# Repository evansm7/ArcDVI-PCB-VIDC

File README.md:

# ArcDVI VIDC push-on PCB

Kicad 6.0 PCB design for the ArcDVI soldered-VIDC push-on board:

This board carries an upturned PTH PLCC68 which plugs onto a soldered VIDC from above.  This should fit an Acorn A3000, but hasn't been mechanically tested with the other soldered-VIDC machine, A5000.  The board exports the buffered signals over FFC to the ArcDVI main PCB.  Mechanically, the main PCB is designed to bolt on top of this board (with appropriate spacers) and fit underneath the floppy drive.

See <https://stardot.org.uk> for more info.

# License

ArcDVI is copyright 2023 Matt Evans.

This work is licensed under the Creative Commons Attribution-NonCommercial-ShareAlike 3.0 Unported License. To view a copy of this license, visit http://creativecommons.org/licenses/by-nc-sa/3.0/ or send a letter to Creative Commons, PO Box 1866, Mountain View, CA 94042, USA.

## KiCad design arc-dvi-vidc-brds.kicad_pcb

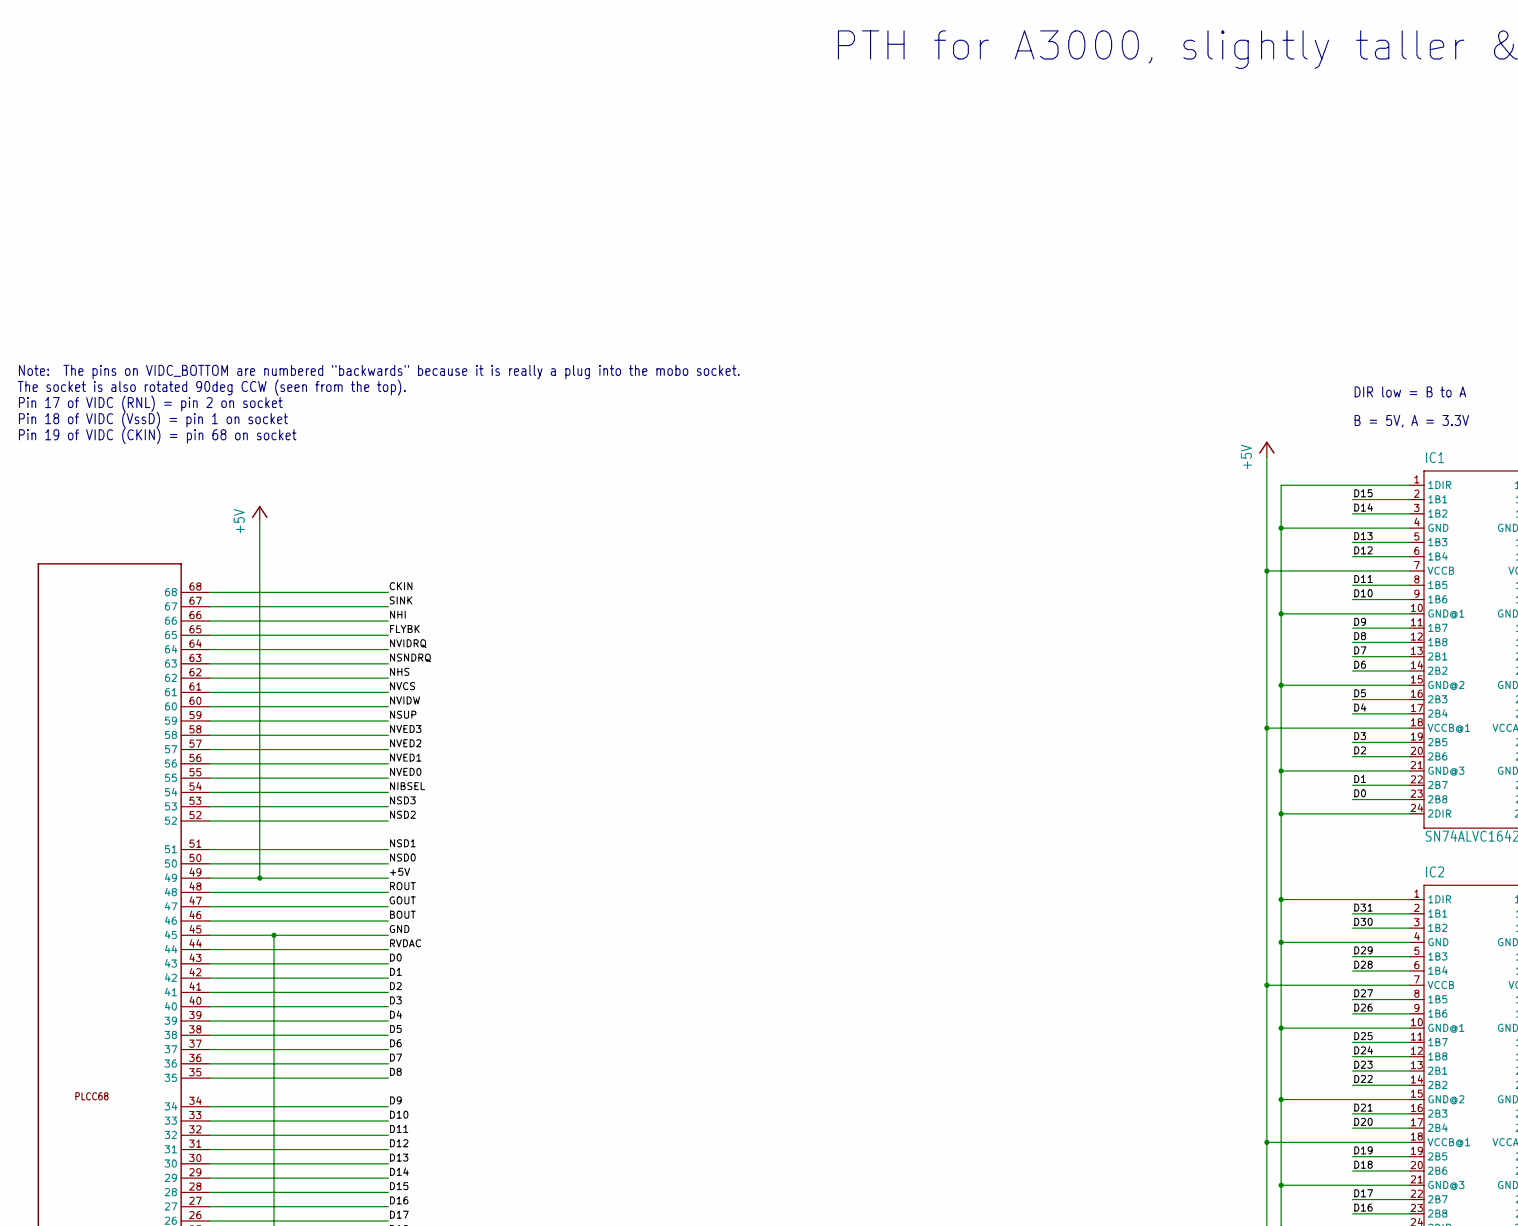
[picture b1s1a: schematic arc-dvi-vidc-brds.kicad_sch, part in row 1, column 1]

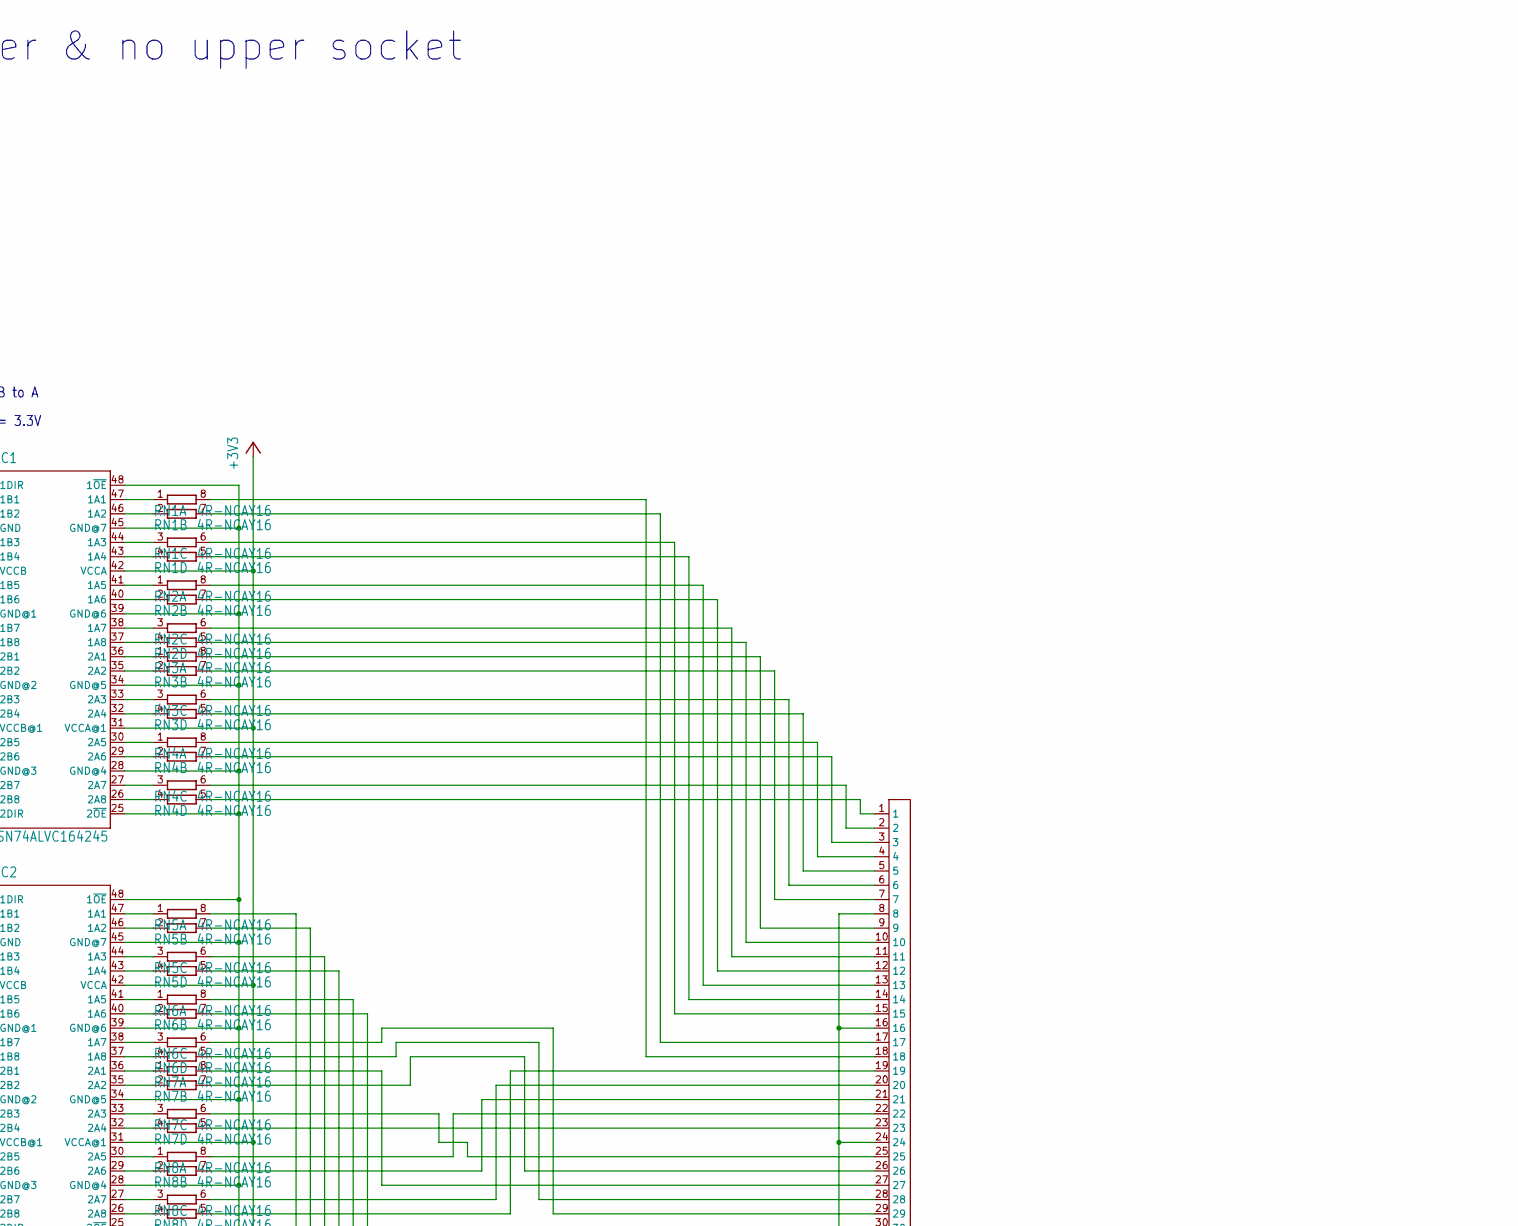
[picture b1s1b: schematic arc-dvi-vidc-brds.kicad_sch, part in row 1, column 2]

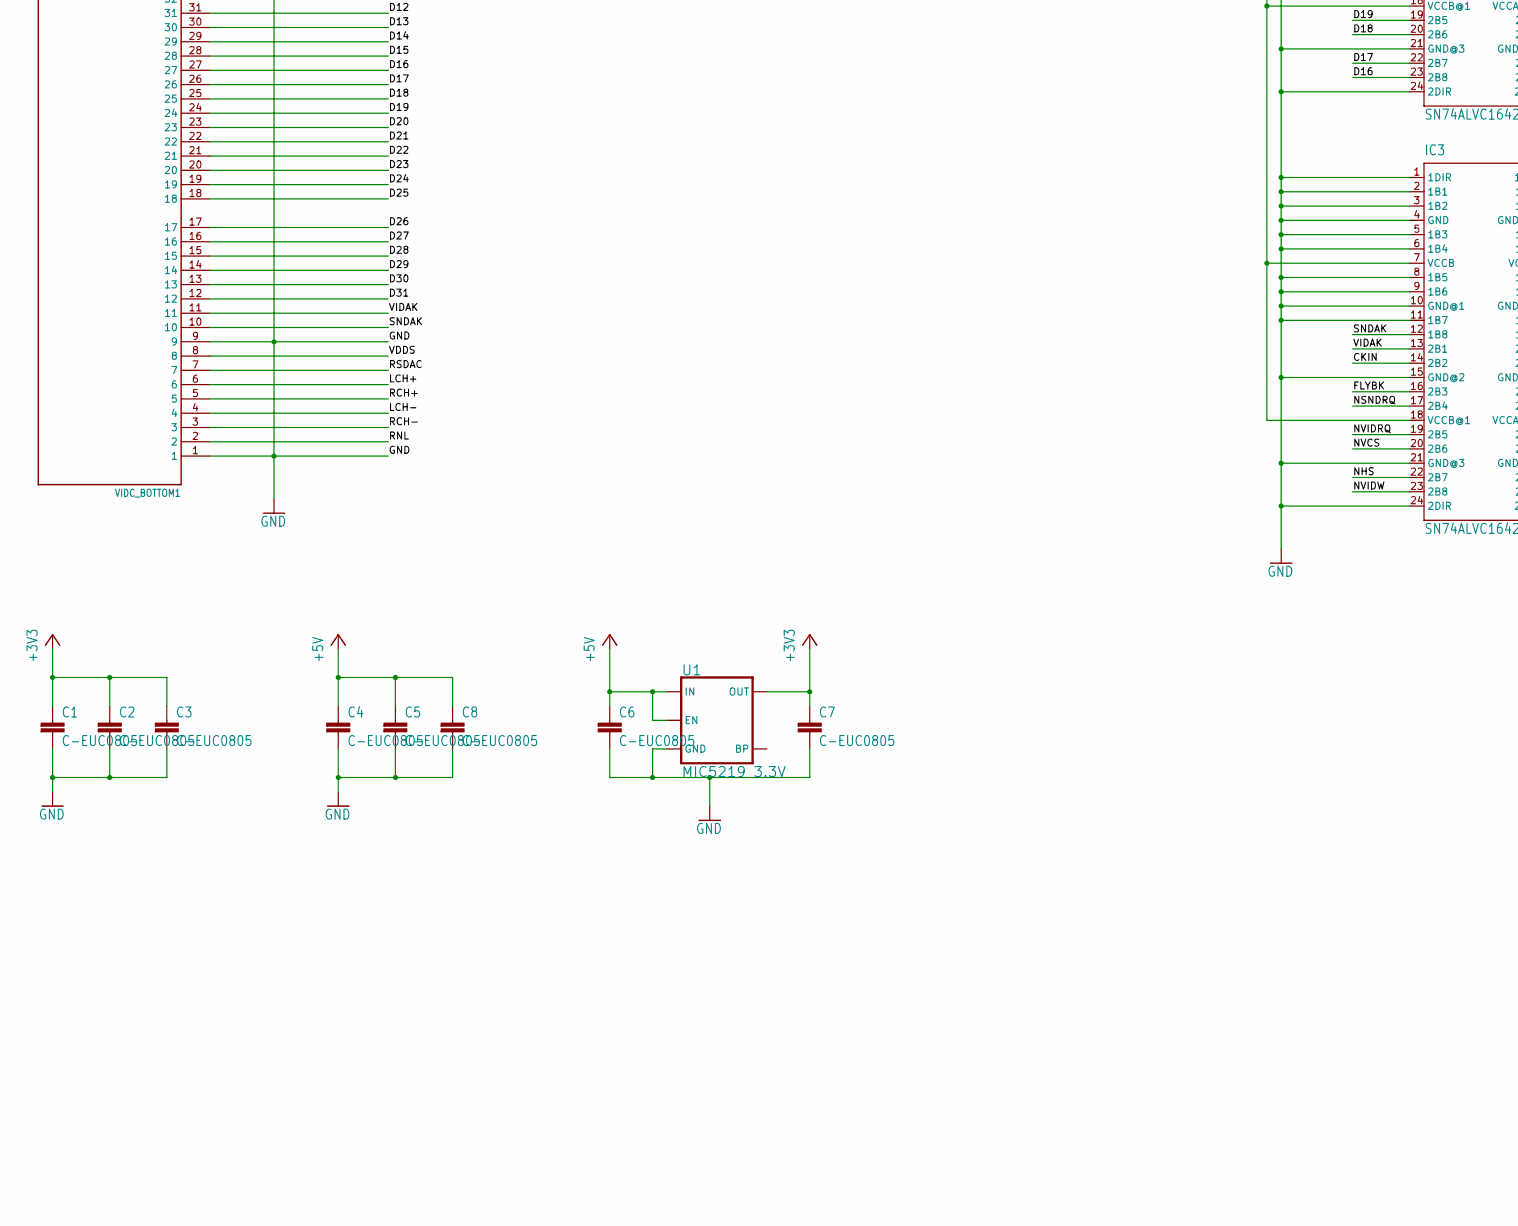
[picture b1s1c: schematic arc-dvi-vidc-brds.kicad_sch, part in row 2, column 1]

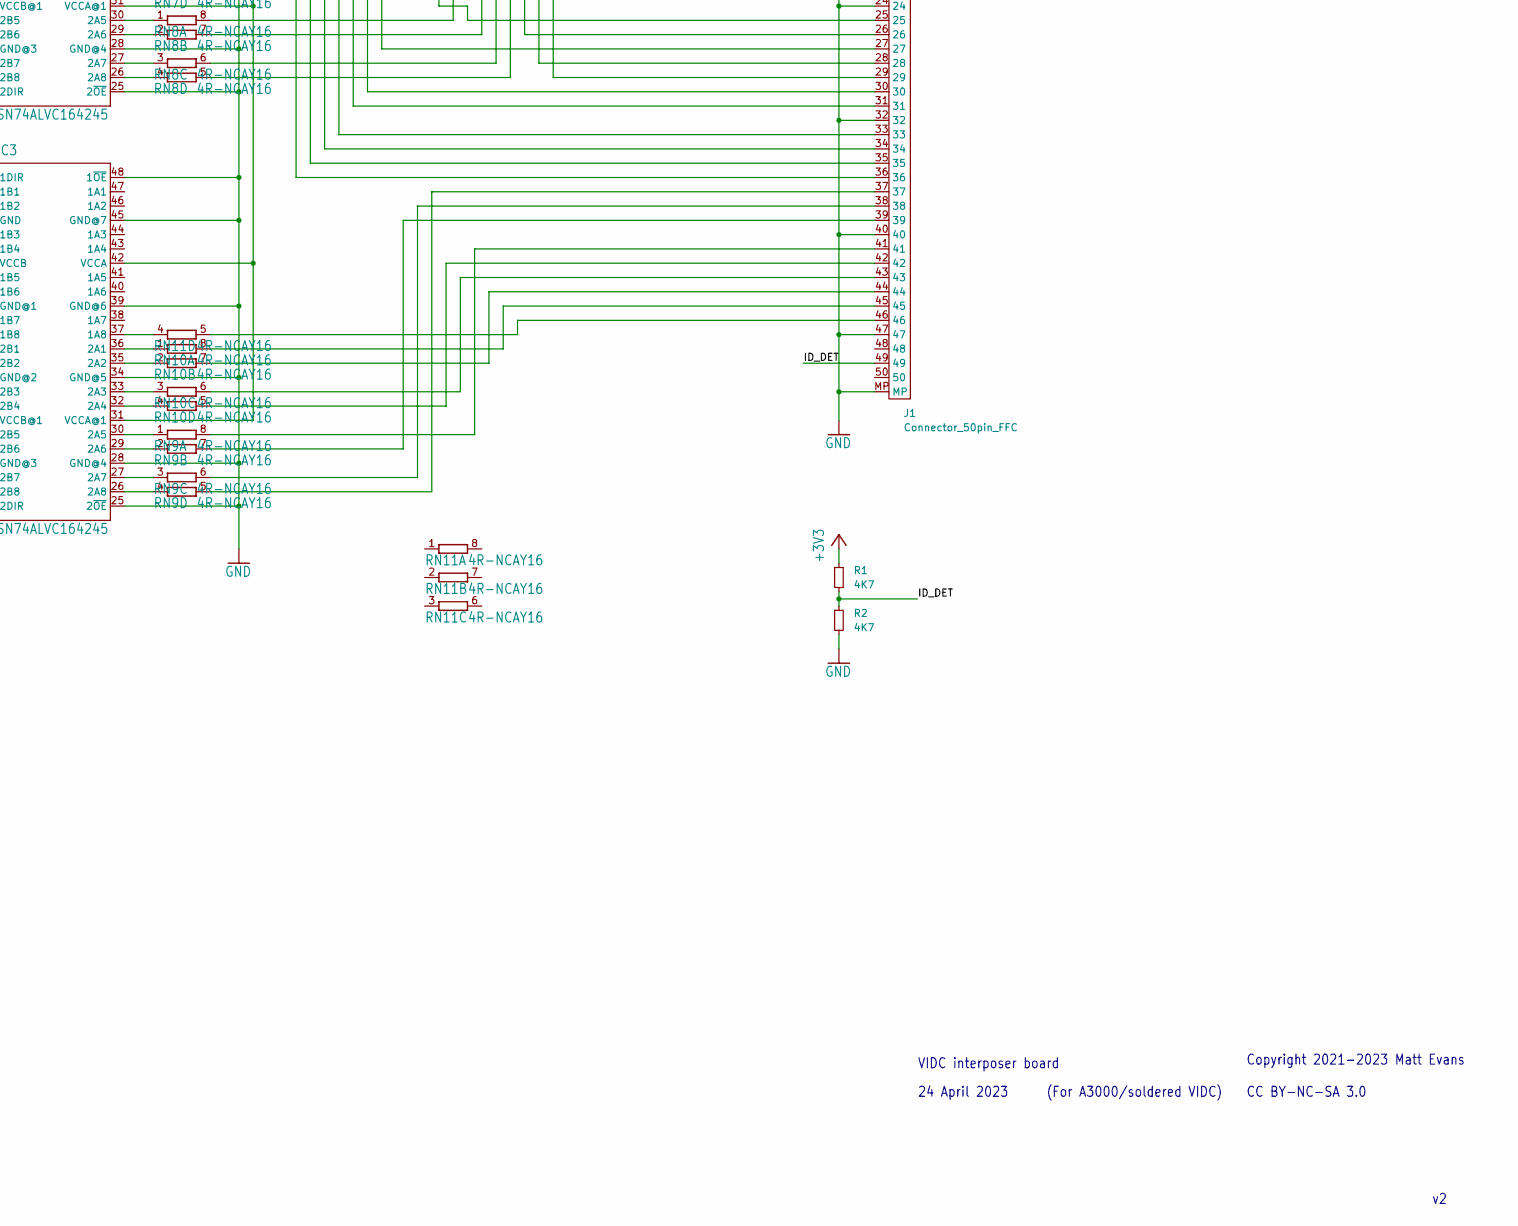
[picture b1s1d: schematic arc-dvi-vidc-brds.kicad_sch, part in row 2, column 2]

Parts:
C1, C2, C3, C4, C5, C6, C7, C8: C-EUC0805; C_0805_2012Metric_Pad1.18x1.45mm_HandSolder
IC1, IC2, IC3: SN74ALVC164245; TSSOP-48_6.1x12.5mm_P0.5mm
J1: Connector_50pin_FFC; Hirose_FH12-50S-0.5SH_1x50-1MP_P0.50mm_Horizontal
R1, R2: 4K7; R_0603_1608Metric
RN1, RN2, RN3, RN4, RN5, RN6, RN7, RN8, RN9, RN10, RN11: 4R-NCAY16; R_Array_Convex_4x0603
U1: MIC5219 3.3V; SOT-23-5
VIDC_BOTTOM1: RAW_PLCC68PTH; PLCC-68_THT-Socket

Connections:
+3V3: C1.1, C2.1, C3.1, C7.1, IC1.31 (VCCA@1), IC1.42 (VCCA), IC2.31 (VCCA@1), IC2.42 (VCCA), IC3.31 (VCCA@1), IC3.42 (VCCA), R1.1, U1.5 (OUT)
+5V: C4.1, C5.1, C6.1, C8.1, IC1.7 (VCCB), IC1.18 (VCCB@1), IC2.7 (VCCB), IC2.18 (VCCB@1), IC3.7 (VCCB), IC3.18 (VCCB@1), U1.1 (IN), U1.3 (EN), VIDC_BOTTOM1.49
/BOUT: VIDC_BOTTOM1.46
/CKIN: IC3.14 (2B2), VIDC_BOTTOM1.68
/D0: IC1.23 (2B8), VIDC_BOTTOM1.43
/D1: IC1.22 (2B7), VIDC_BOTTOM1.42
/D2: IC1.20 (2B6), VIDC_BOTTOM1.41
/D3: IC1.19 (2B5), VIDC_BOTTOM1.40
/D4: IC1.17 (2B4), VIDC_BOTTOM1.39
/D5: IC1.16 (2B3), VIDC_BOTTOM1.38
/D6: IC1.14 (2B2), VIDC_BOTTOM1.37
/D7: IC1.13 (2B1), VIDC_BOTTOM1.36
/D8: IC1.12 (1B8), VIDC_BOTTOM1.35
/D9: IC1.11 (1B7), VIDC_BOTTOM1.34
/D10: IC1.9 (1B6), VIDC_BOTTOM1.33
/D11: IC1.8 (1B5), VIDC_BOTTOM1.32
/D12: IC1.6 (1B4), VIDC_BOTTOM1.31
/D13: IC1.5 (1B3), VIDC_BOTTOM1.30
/D14: IC1.3 (1B2), VIDC_BOTTOM1.29
/D15: IC1.2 (1B1), VIDC_BOTTOM1.28
/D16: IC2.23 (2B8), VIDC_BOTTOM1.27
/D17: IC2.22 (2B7), VIDC_BOTTOM1.26
/D18: IC2.20 (2B6), VIDC_BOTTOM1.25
/D19: IC2.19 (2B5), VIDC_BOTTOM1.24
/D20: IC2.17 (2B4), VIDC_BOTTOM1.23
/D21: IC2.16 (2B3), VIDC_BOTTOM1.22
/D22: IC2.14 (2B2), VIDC_BOTTOM1.21
/D23: IC2.13 (2B1), VIDC_BOTTOM1.20
/D24: IC2.12 (1B8), VIDC_BOTTOM1.19
/D25: IC2.11 (1B7), VIDC_BOTTOM1.18
/D26: IC2.9 (1B6), VIDC_BOTTOM1.17
/D27: IC2.8 (1B5), VIDC_BOTTOM1.16
/D28: IC2.6 (1B4), VIDC_BOTTOM1.15
/D29: IC2.5 (1B3), VIDC_BOTTOM1.14
/D30: IC2.3 (1B2), VIDC_BOTTOM1.13
/D31: IC2.2 (1B1), VIDC_BOTTOM1.12
/FLYBK: IC3.16 (2B3), VIDC_BOTTOM1.65
/GOUT: VIDC_BOTTOM1.47
/ID_DET: J1.49, R1.2, R2.1
/LCH+: VIDC_BOTTOM1.6
/LCH-: VIDC_BOTTOM1.4
/NHI: VIDC_BOTTOM1.66
/NHS: IC3.22 (2B7), VIDC_BOTTOM1.62
/NIBSEL: VIDC_BOTTOM1.54
/NSD0: VIDC_BOTTOM1.50
/NSD1: VIDC_BOTTOM1.51
/NSD2: VIDC_BOTTOM1.52
/NSD3: VIDC_BOTTOM1.53
/NSNDRQ: IC3.17 (2B4), VIDC_BOTTOM1.63
/NSUP: VIDC_BOTTOM1.59
/NVCS: IC3.20 (2B6), VIDC_BOTTOM1.61
/NVED0: VIDC_BOTTOM1.55
/NVED1: VIDC_BOTTOM1.56
/NVED2: VIDC_BOTTOM1.57
/NVED3: VIDC_BOTTOM1.58
/NVIDRQ: IC3.19 (2B5), VIDC_BOTTOM1.64
/NVIDW: IC3.23 (2B8), VIDC_BOTTOM1.60
/RCH+: VIDC_BOTTOM1.5
/RCH-: VIDC_BOTTOM1.3
/RNL: VIDC_BOTTOM1.2
/ROUT: VIDC_BOTTOM1.48
/RSDAC: VIDC_BOTTOM1.7
/RVDAC: VIDC_BOTTOM1.44
/SINK: VIDC_BOTTOM1.67
/SNDAK: IC3.12 (1B8), VIDC_BOTTOM1.10
/VDDS: VIDC_BOTTOM1.8
/VIDAK: IC3.13 (2B1), VIDC_BOTTOM1.11
GND: C1.2, C2.2, C3.2, C4.2, C5.2, C6.2, C7.2, C8.2, IC1.1 (1DIR), IC1.4 (GND), IC1.10 (GND@1), IC1.15 (GND@2), IC1.21 (GND@3), IC1.24 (2DIR), IC1.25 (2~OE), IC1.28 (GND@4), IC1.34 (GND@5), IC1.39 (GND@6), IC1.45 (GND@7), IC1.48 (1~OE), IC2.1 (1DIR), IC2.4 (GND), IC2.10 (GND@1), IC2.15 (GND@2), IC2.21 (GND@3), IC2.24 (2DIR), IC2.25 (2~OE), IC2.28 (GND@4), IC2.34 (GND@5), IC2.39 (GND@6), IC2.45 (GND@7), IC2.48 (1~OE), IC3.1 (1DIR), IC3.2 (1B1), IC3.3 (1B2), IC3.4 (GND), IC3.5 (1B3), IC3.6 (1B4), IC3.8 (1B5), IC3.9 (1B6), IC3.10 (GND@1), IC3.11 (1B7), IC3.15 (GND@2), IC3.21 (GND@3), IC3.24 (2DIR), IC3.25 (2~OE), IC3.28 (GND@4), IC3.34 (GND@5), IC3.39 (GND@6), IC3.45 (GND@7), IC3.48 (1~OE), J1.8, J1.16, J1.24, J1.32, J1.40, J1.47, J1.MP, R2.2, U1.2 (GND), VIDC_BOTTOM1.1, VIDC_BOTTOM1.9, VIDC_BOTTOM1.45
unnamed: IC1.26 (2A8), RN4.4 (1)
unnamed: IC1.27 (2A7), RN4.3 (1)
unnamed: IC1.29 (2A6), RN4.2 (1)
unnamed: IC1.30 (2A5), RN4.1
unnamed: IC1.32 (2A4), RN3.4 (1)
unnamed: IC1.33 (2A3), RN3.3 (1)
unnamed: IC1.35 (2A2), RN3.2 (1)
unnamed: IC1.36 (2A1), RN3.1
unnamed: IC1.37 (1A8), RN2.4 (1)
unnamed: IC1.38 (1A7), RN2.3 (1)
unnamed: IC1.40 (1A6), RN2.2 (1)
unnamed: IC1.41 (1A5), RN2.1
unnamed: IC1.43 (1A4), RN1.4 (1)
unnamed: IC1.44 (1A3), RN1.3 (1)
unnamed: IC1.46 (1A2), RN1.2 (1)
unnamed: IC1.47 (1A1), RN1.1
unnamed: IC2.26 (2A8), RN8.4 (1)
unnamed: IC2.27 (2A7), RN8.3 (1)
unnamed: IC2.29 (2A6), RN8.2 (1)
unnamed: IC2.30 (2A5), RN8.1
unnamed: IC2.32 (2A4), RN7.4 (1)
unnamed: IC2.33 (2A3), RN7.3 (1)
unnamed: IC2.35 (2A2), RN7.2 (1)
unnamed: IC2.36 (2A1), RN7.1
unnamed: IC2.37 (1A8), RN6.4 (1)
unnamed: IC2.38 (1A7), RN6.3 (1)
unnamed: IC2.40 (1A6), RN6.2 (1)
unnamed: IC2.41 (1A5), RN6.1
unnamed: IC2.43 (1A4), RN5.4 (1)
unnamed: IC2.44 (1A3), RN5.3 (1)
unnamed: IC2.46 (1A2), RN5.2 (1)
unnamed: IC2.47 (1A1), RN5.1
unnamed: IC3.26 (2A8), RN9.4 (1)
unnamed: IC3.27 (2A7), RN9.3 (1)
unnamed: IC3.29 (2A6), RN9.2 (1)
unnamed: IC3.30 (2A5), RN9.1
unnamed: IC3.32 (2A4), RN10.4 (1)
unnamed: IC3.33 (2A3), RN10.3 (1)
unnamed: IC3.35 (2A2), RN10.2 (1)
unnamed: IC3.36 (2A1), RN10.1
unnamed: IC3.37 (1A8), RN11.4 (1)
unnamed: J1.1, RN4.5 (2)
unnamed: J1.2, RN4.6 (2)
unnamed: J1.3, RN4.7 (2)
unnamed: J1.4, RN4.8 (2)
unnamed: J1.5, RN3.5 (2)
unnamed: J1.6, RN3.6 (2)
unnamed: J1.7, RN3.7 (2)
unnamed: J1.9, RN3.8 (2)
unnamed: J1.10, RN2.5 (2)
unnamed: J1.11, RN2.6 (2)
unnamed: J1.12, RN2.7 (2)
unnamed: J1.13, RN2.8 (2)
unnamed: J1.14, RN1.5 (2)
unnamed: J1.15, RN1.6 (2)
unnamed: J1.17, RN1.7 (2)
unnamed: J1.18, RN1.8 (2)
unnamed: J1.19, RN8.5 (2)
unnamed: J1.20, RN8.6 (2)
unnamed: J1.21, RN8.7 (2)
unnamed: J1.22, RN8.8 (2)
unnamed: J1.23, RN7.5 (2)
unnamed: J1.25, RN7.6 (2)
unnamed: J1.26, RN7.7 (2)
unnamed: J1.27, RN7.8 (2)
unnamed: J1.28, RN6.5 (2)
unnamed: J1.29, RN6.6 (2)
unnamed: J1.30, RN6.7 (2)
unnamed: J1.31, RN6.8 (2)
unnamed: J1.33, RN5.5 (2)
unnamed: J1.34, RN5.6 (2)
unnamed: J1.35, RN5.7 (2)
unnamed: J1.36, RN5.8 (2)
unnamed: J1.37, RN9.5 (2)
unnamed: J1.38, RN9.6 (2)
unnamed: J1.39, RN9.7 (2)
unnamed: J1.41, RN9.8 (2)
unnamed: J1.42, RN10.5 (2)
unnamed: J1.43, RN10.6 (2)
unnamed: J1.44, RN10.7 (2)
unnamed: J1.45, RN10.8 (2)
unnamed: J1.46, RN11.5 (2)

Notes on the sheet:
VIDC interposer board
(For A3000/soldered VIDC)
DIR low = B to A
PTH for A3000, slightly taller & no upper socket~{}
24 April 2023
B = 5V, A = 3.3V
Copyright 2021-2023 Matt Evans CC BY-NC-SA 3.0
Note: The pins on VIDC_BOTTOM are numbered "backwards" because it is really a plug into the mobo socket. The socket is also rotated 90deg CCW (seen from the top). Pin 17 of VIDC (RNL) = pin 2 on socket Pin 18 of VIDC (VssD) = pin 1 on socket Pin 19 of VIDC (CKIN) = pin 68 on socket

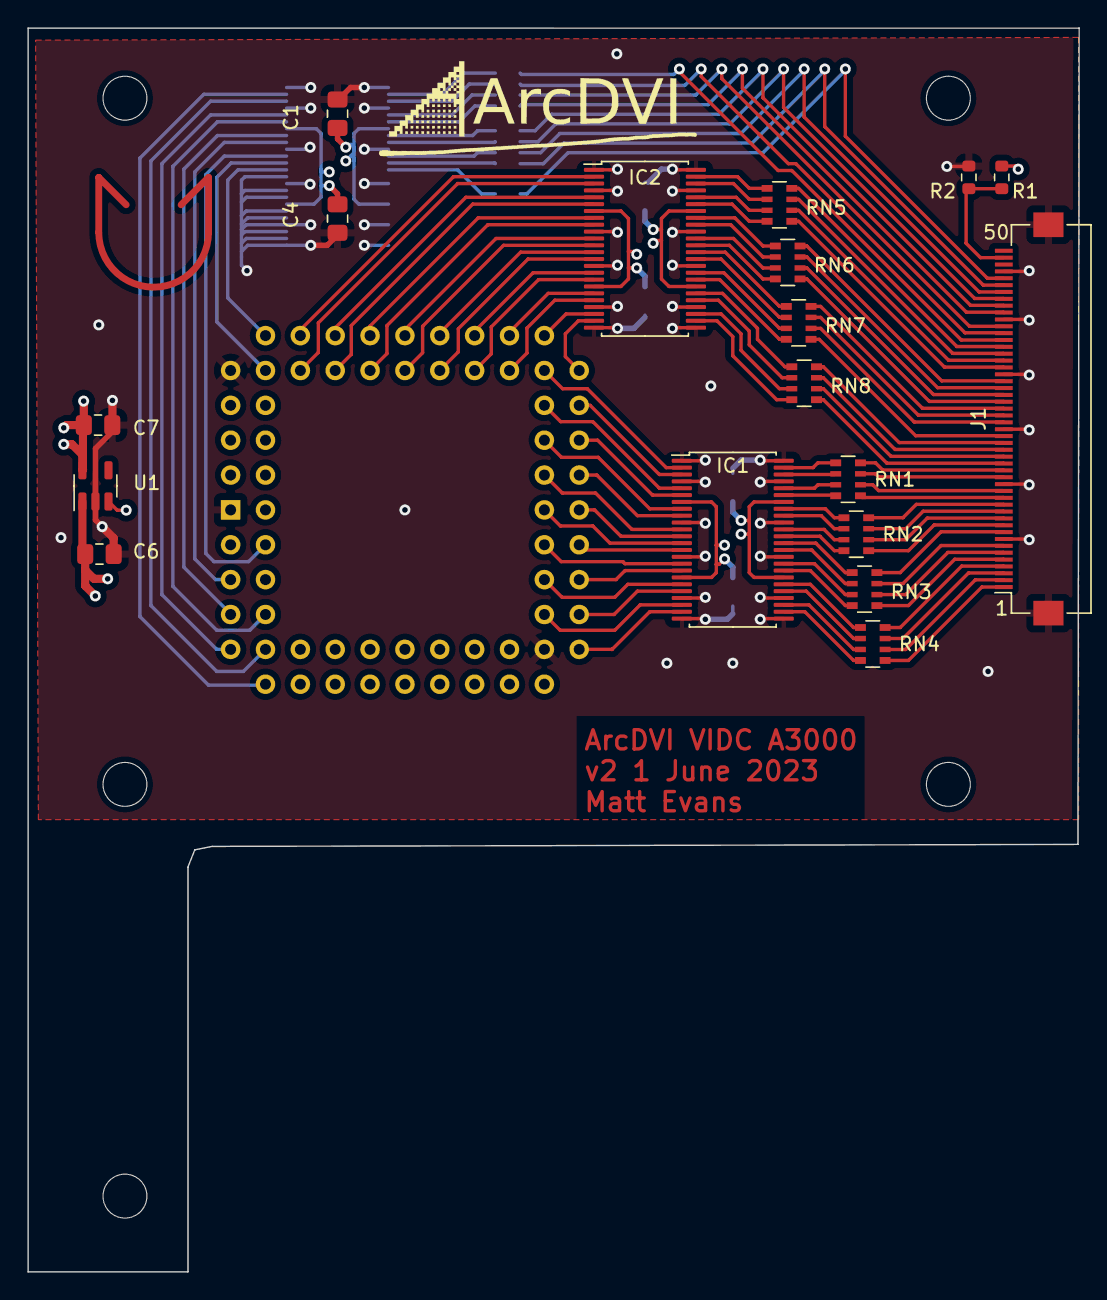
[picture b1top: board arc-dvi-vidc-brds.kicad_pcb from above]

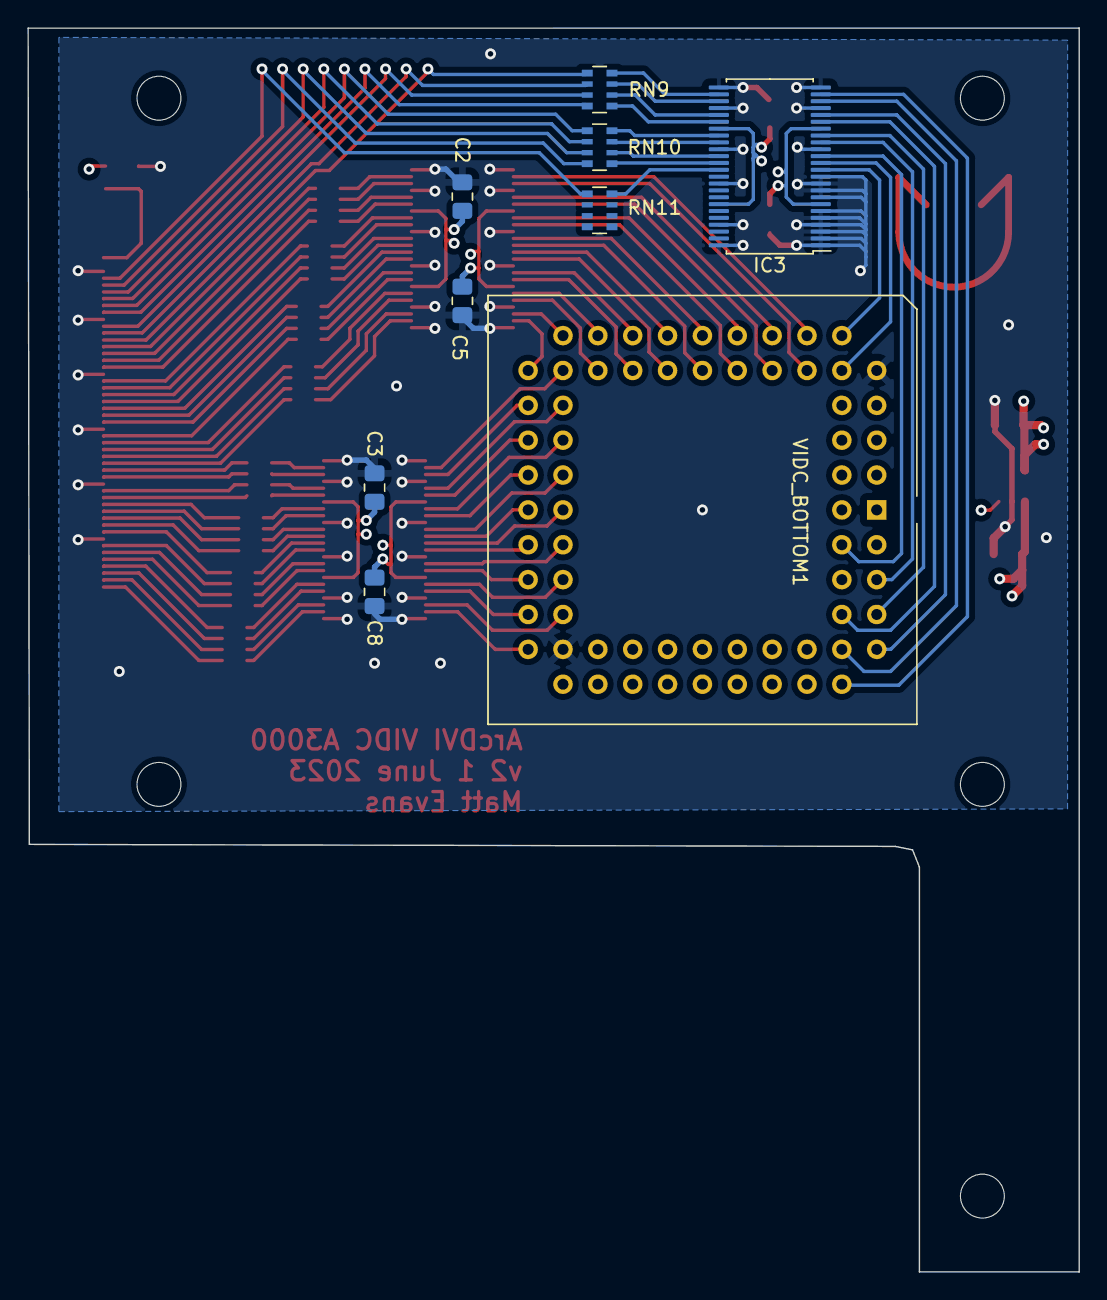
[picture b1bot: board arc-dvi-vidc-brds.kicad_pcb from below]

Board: 4 copper layers, 76.6 x 90.6 mm, 27 parts (9 on the bottom side), 127 nets.

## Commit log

2023-03-09 Board imported from Eagle, rerouted
    Now using FFC-50
2023-04-24 Pretty much finished
    Not DRC'd though, FIXME. Routed, with dimensions measured from
    A3000/FDD spacing etc. Includes extra 80mm holes to mount the
    podule board under FDD too.
2023-05-07 DRC clean
2023-05-11 Tweaks to cap positions, power planes
    Good to go
2023-05-14 Add logo
2023-06-01 Moved holes to 60mm centers
2023-06-01 Update date
2023-06-01 Move regulator, move holes
    Reg move now makes PLCC socket centre bare, ideal for mechanical pressure point.
    Holes now mean main ArcDVI board lines up preciselyish.
2023-06-11 Tweaks to cap positions, power planes
    In good shape now, a few minor tweaks to go
2023-06-11 Remove sym-lib-table
2023-06-11 Add README, licence
